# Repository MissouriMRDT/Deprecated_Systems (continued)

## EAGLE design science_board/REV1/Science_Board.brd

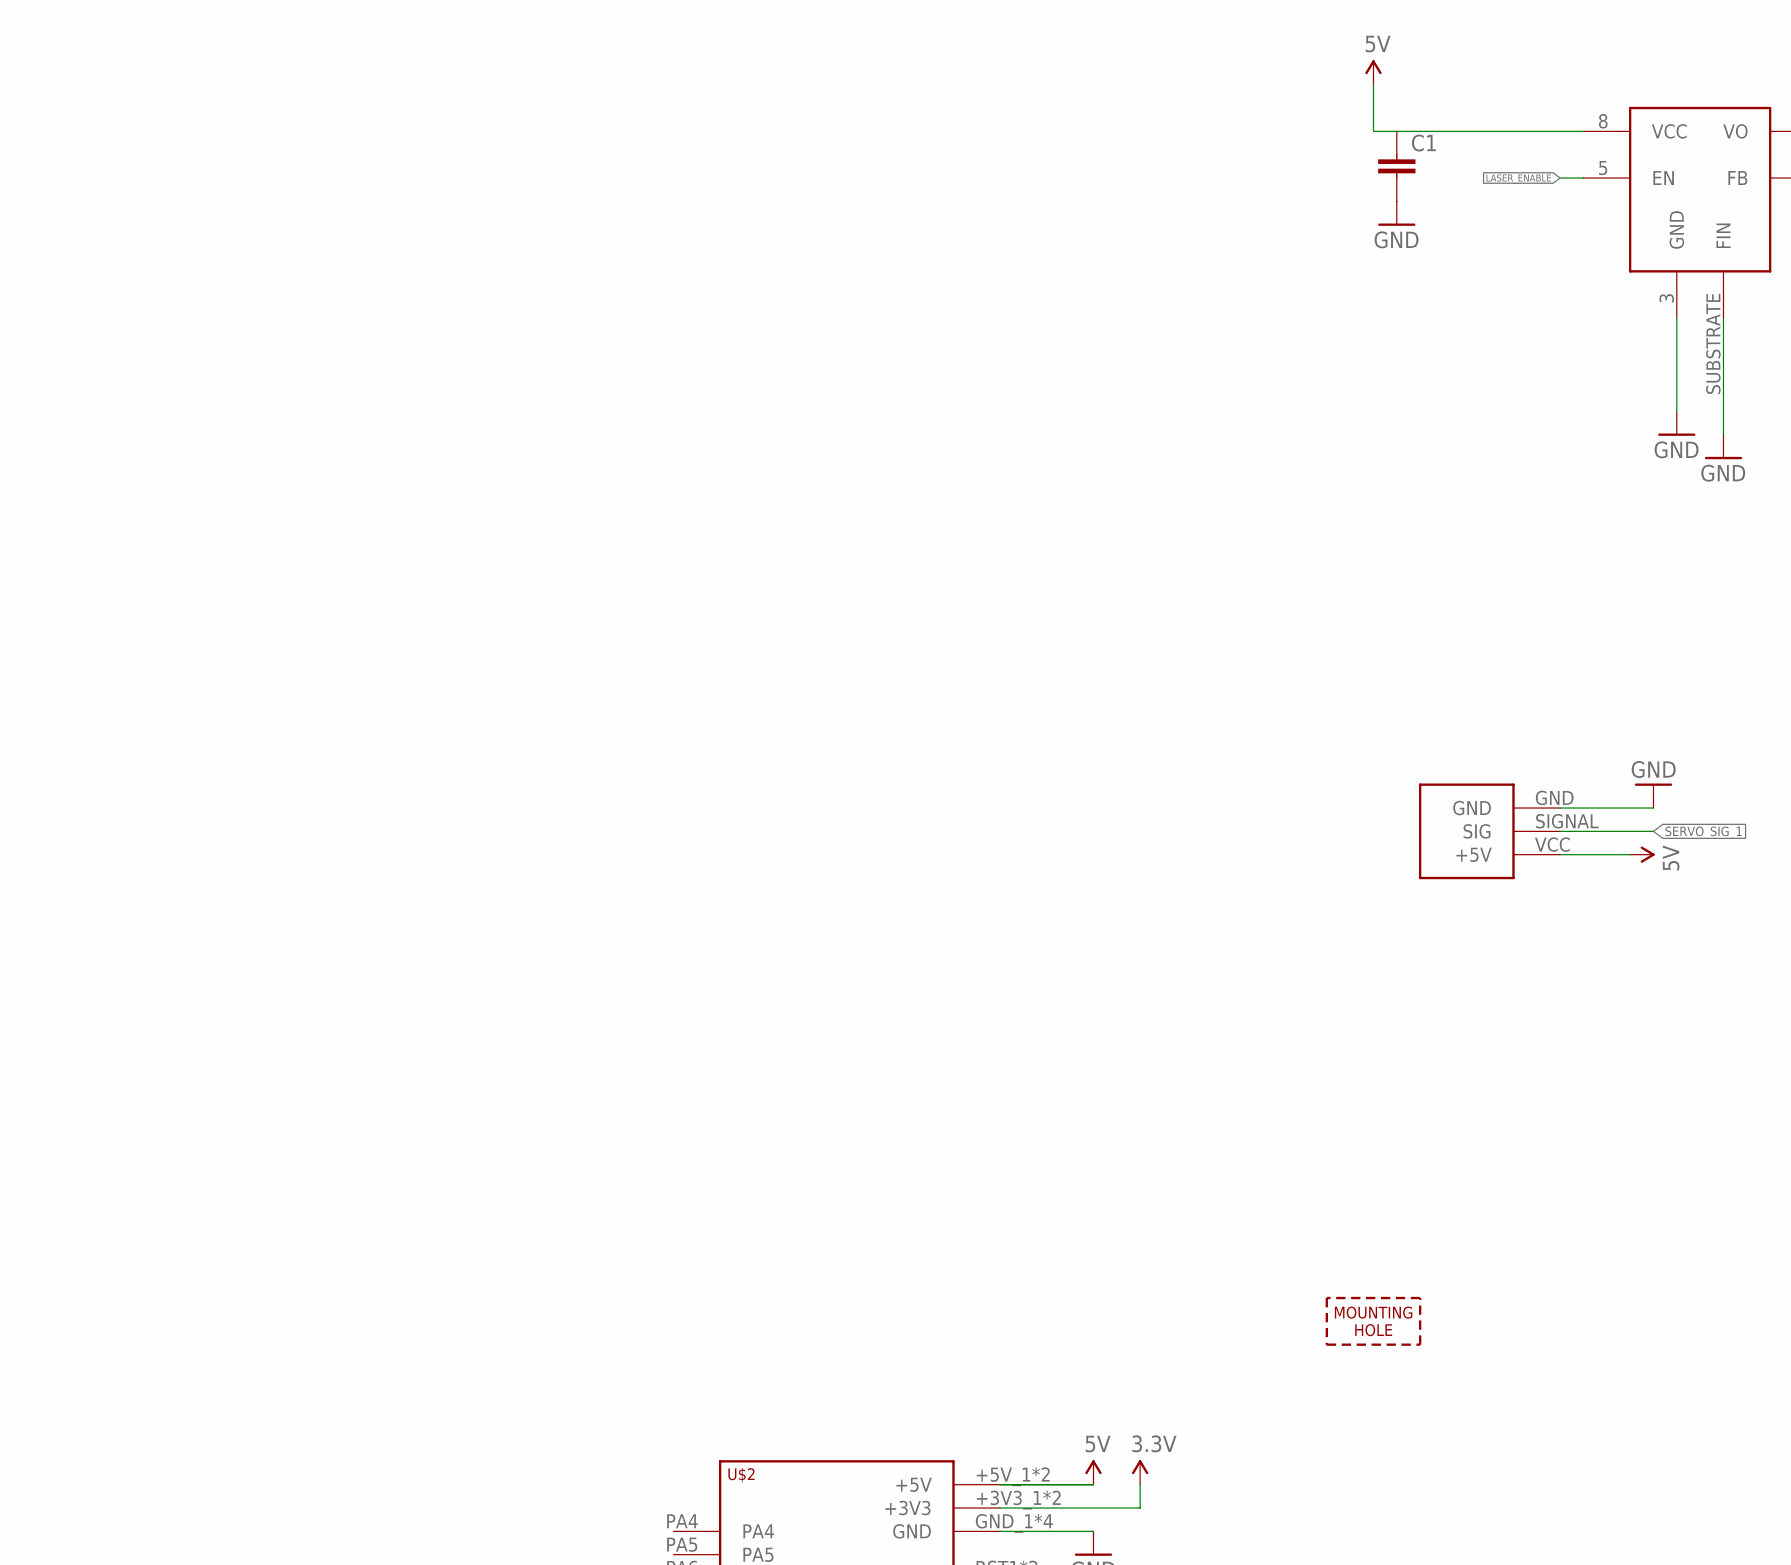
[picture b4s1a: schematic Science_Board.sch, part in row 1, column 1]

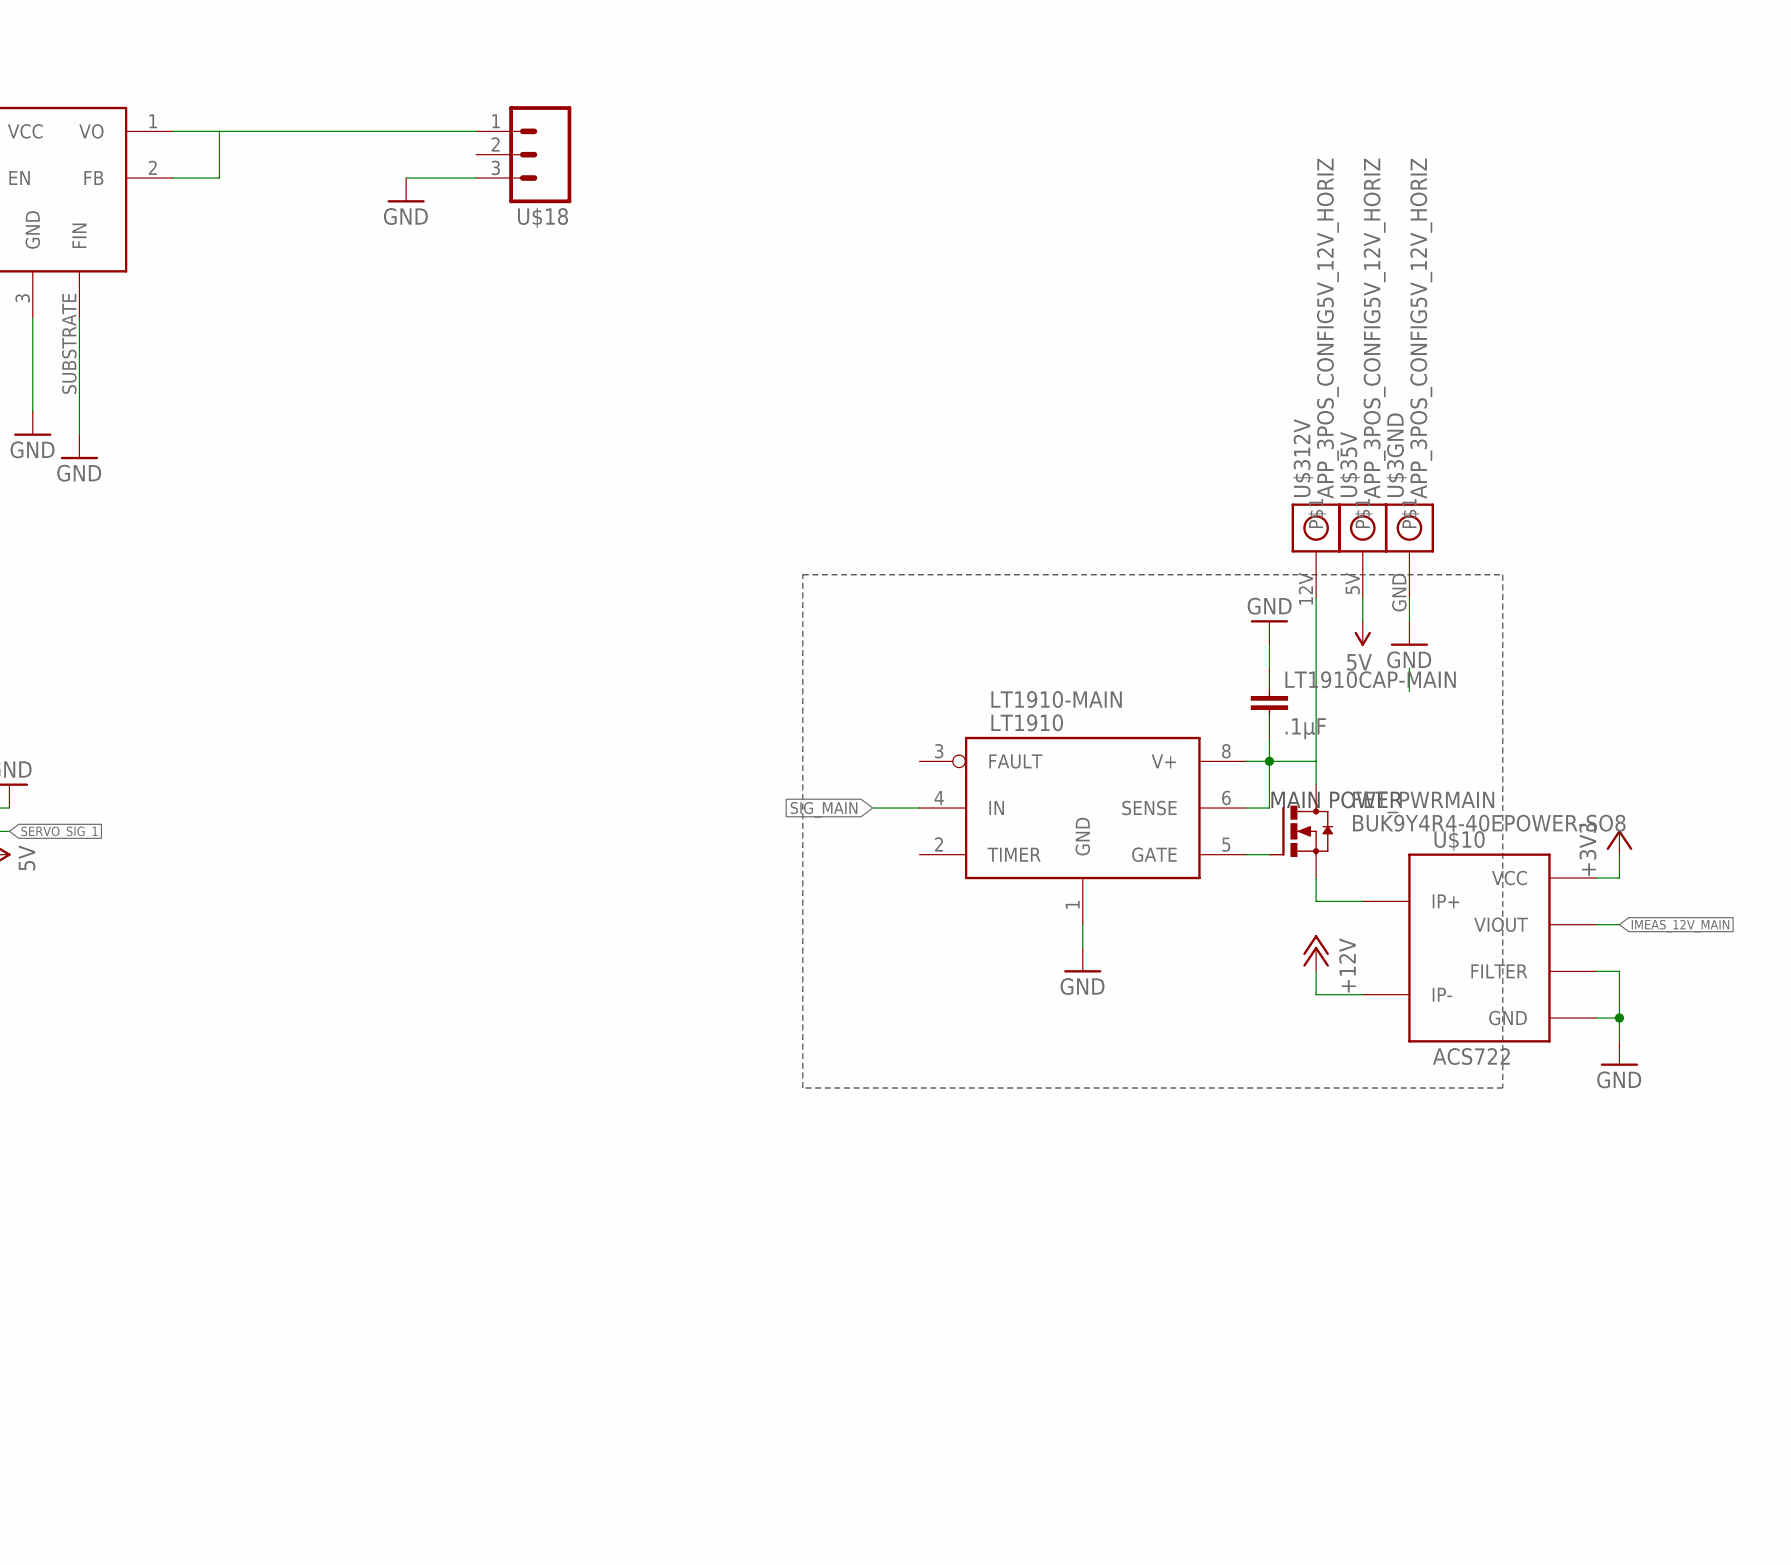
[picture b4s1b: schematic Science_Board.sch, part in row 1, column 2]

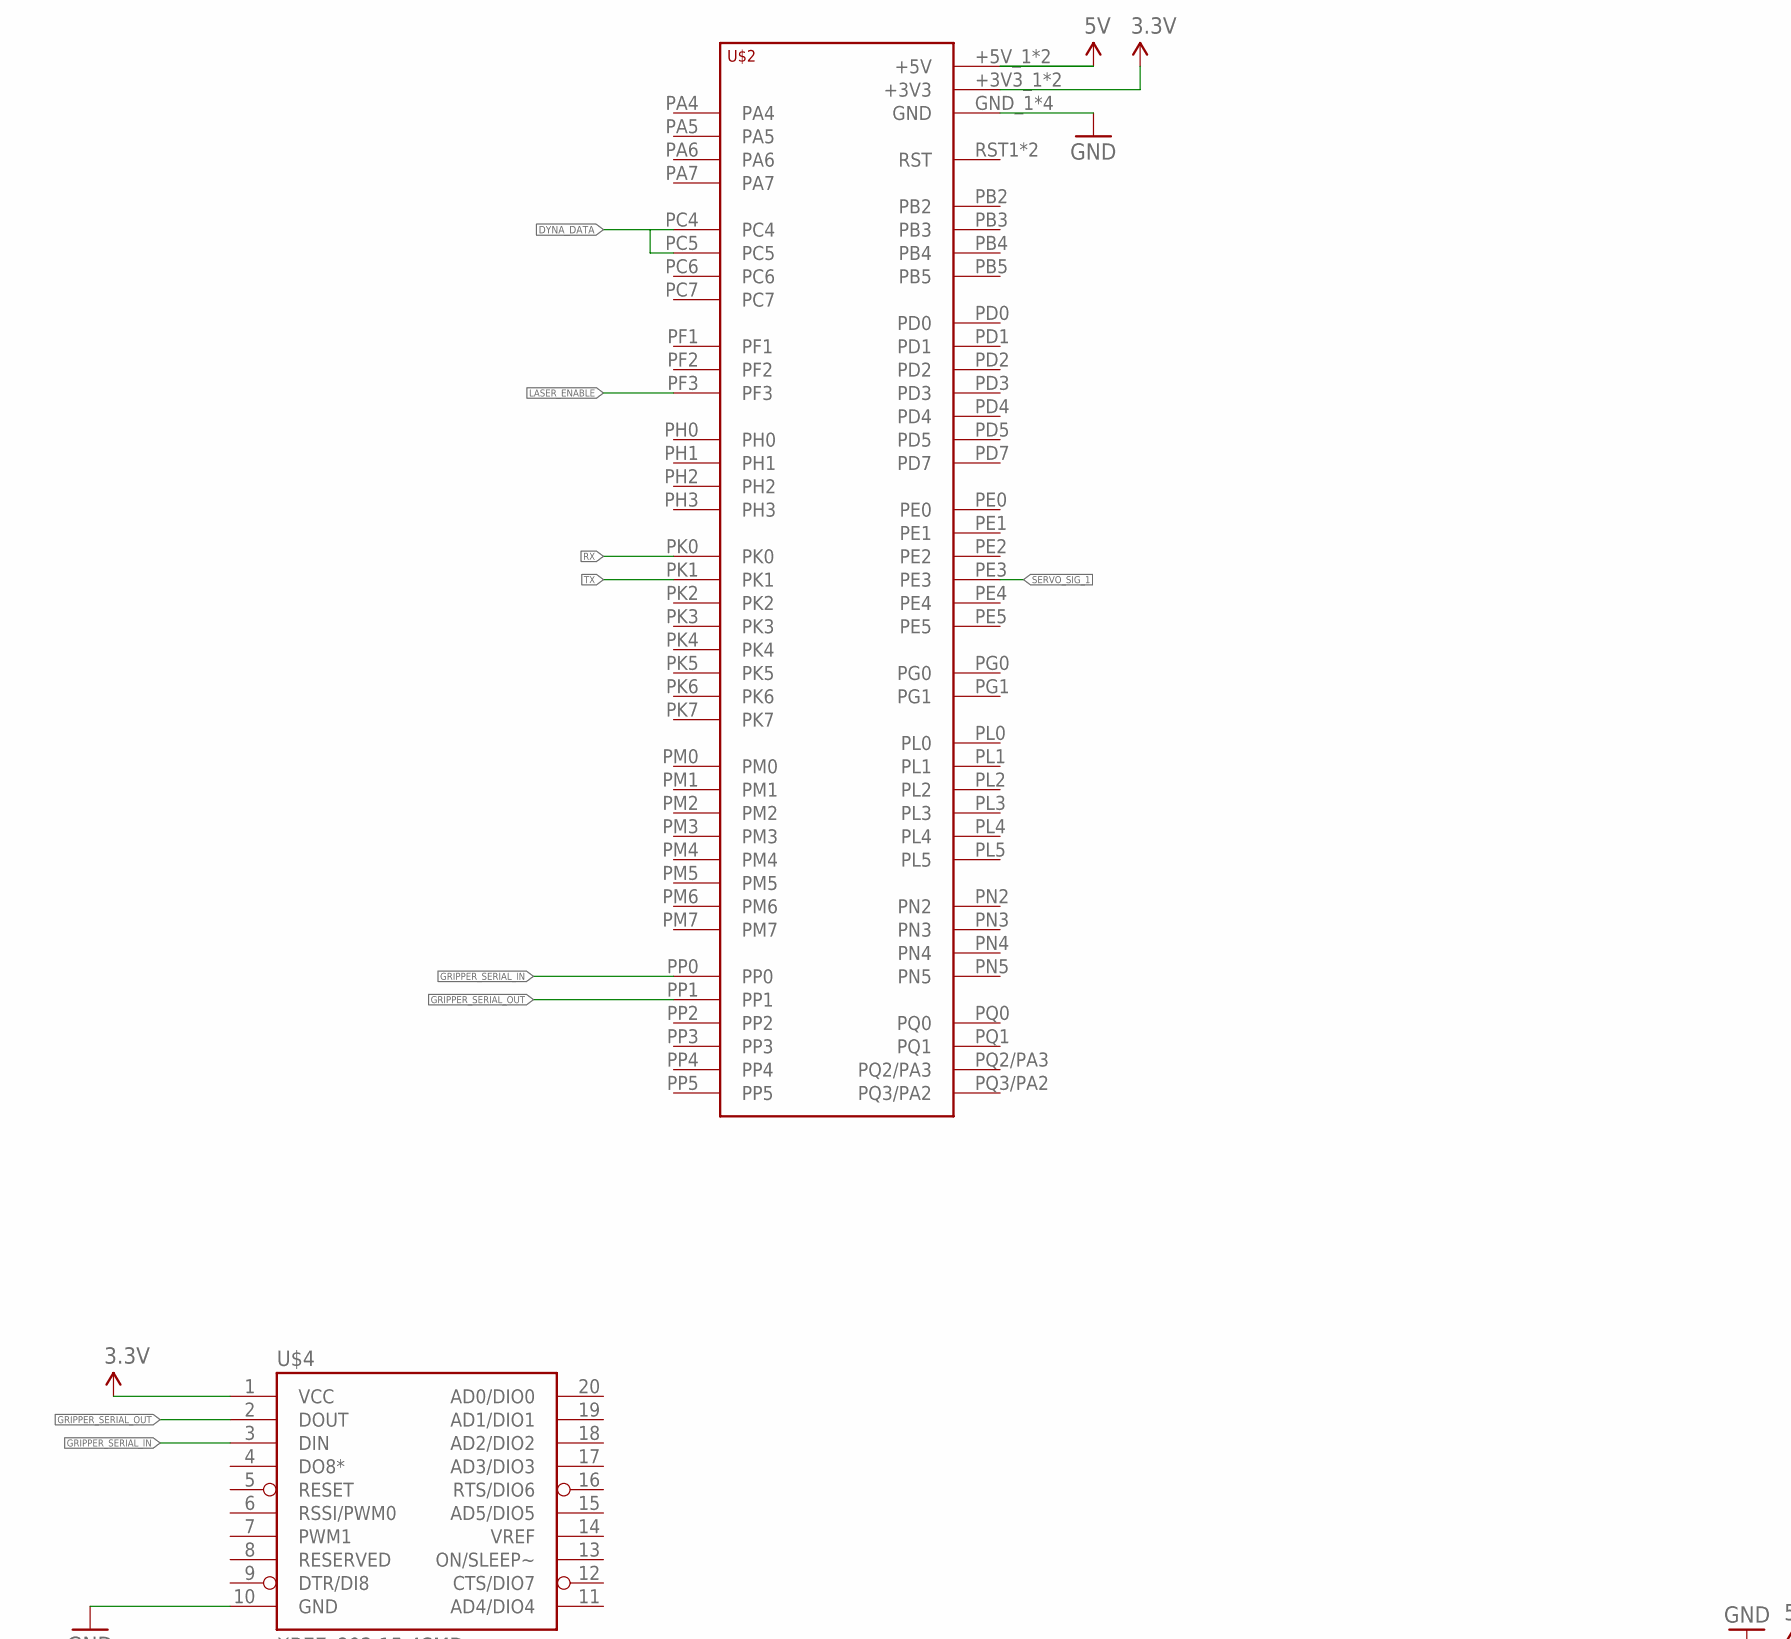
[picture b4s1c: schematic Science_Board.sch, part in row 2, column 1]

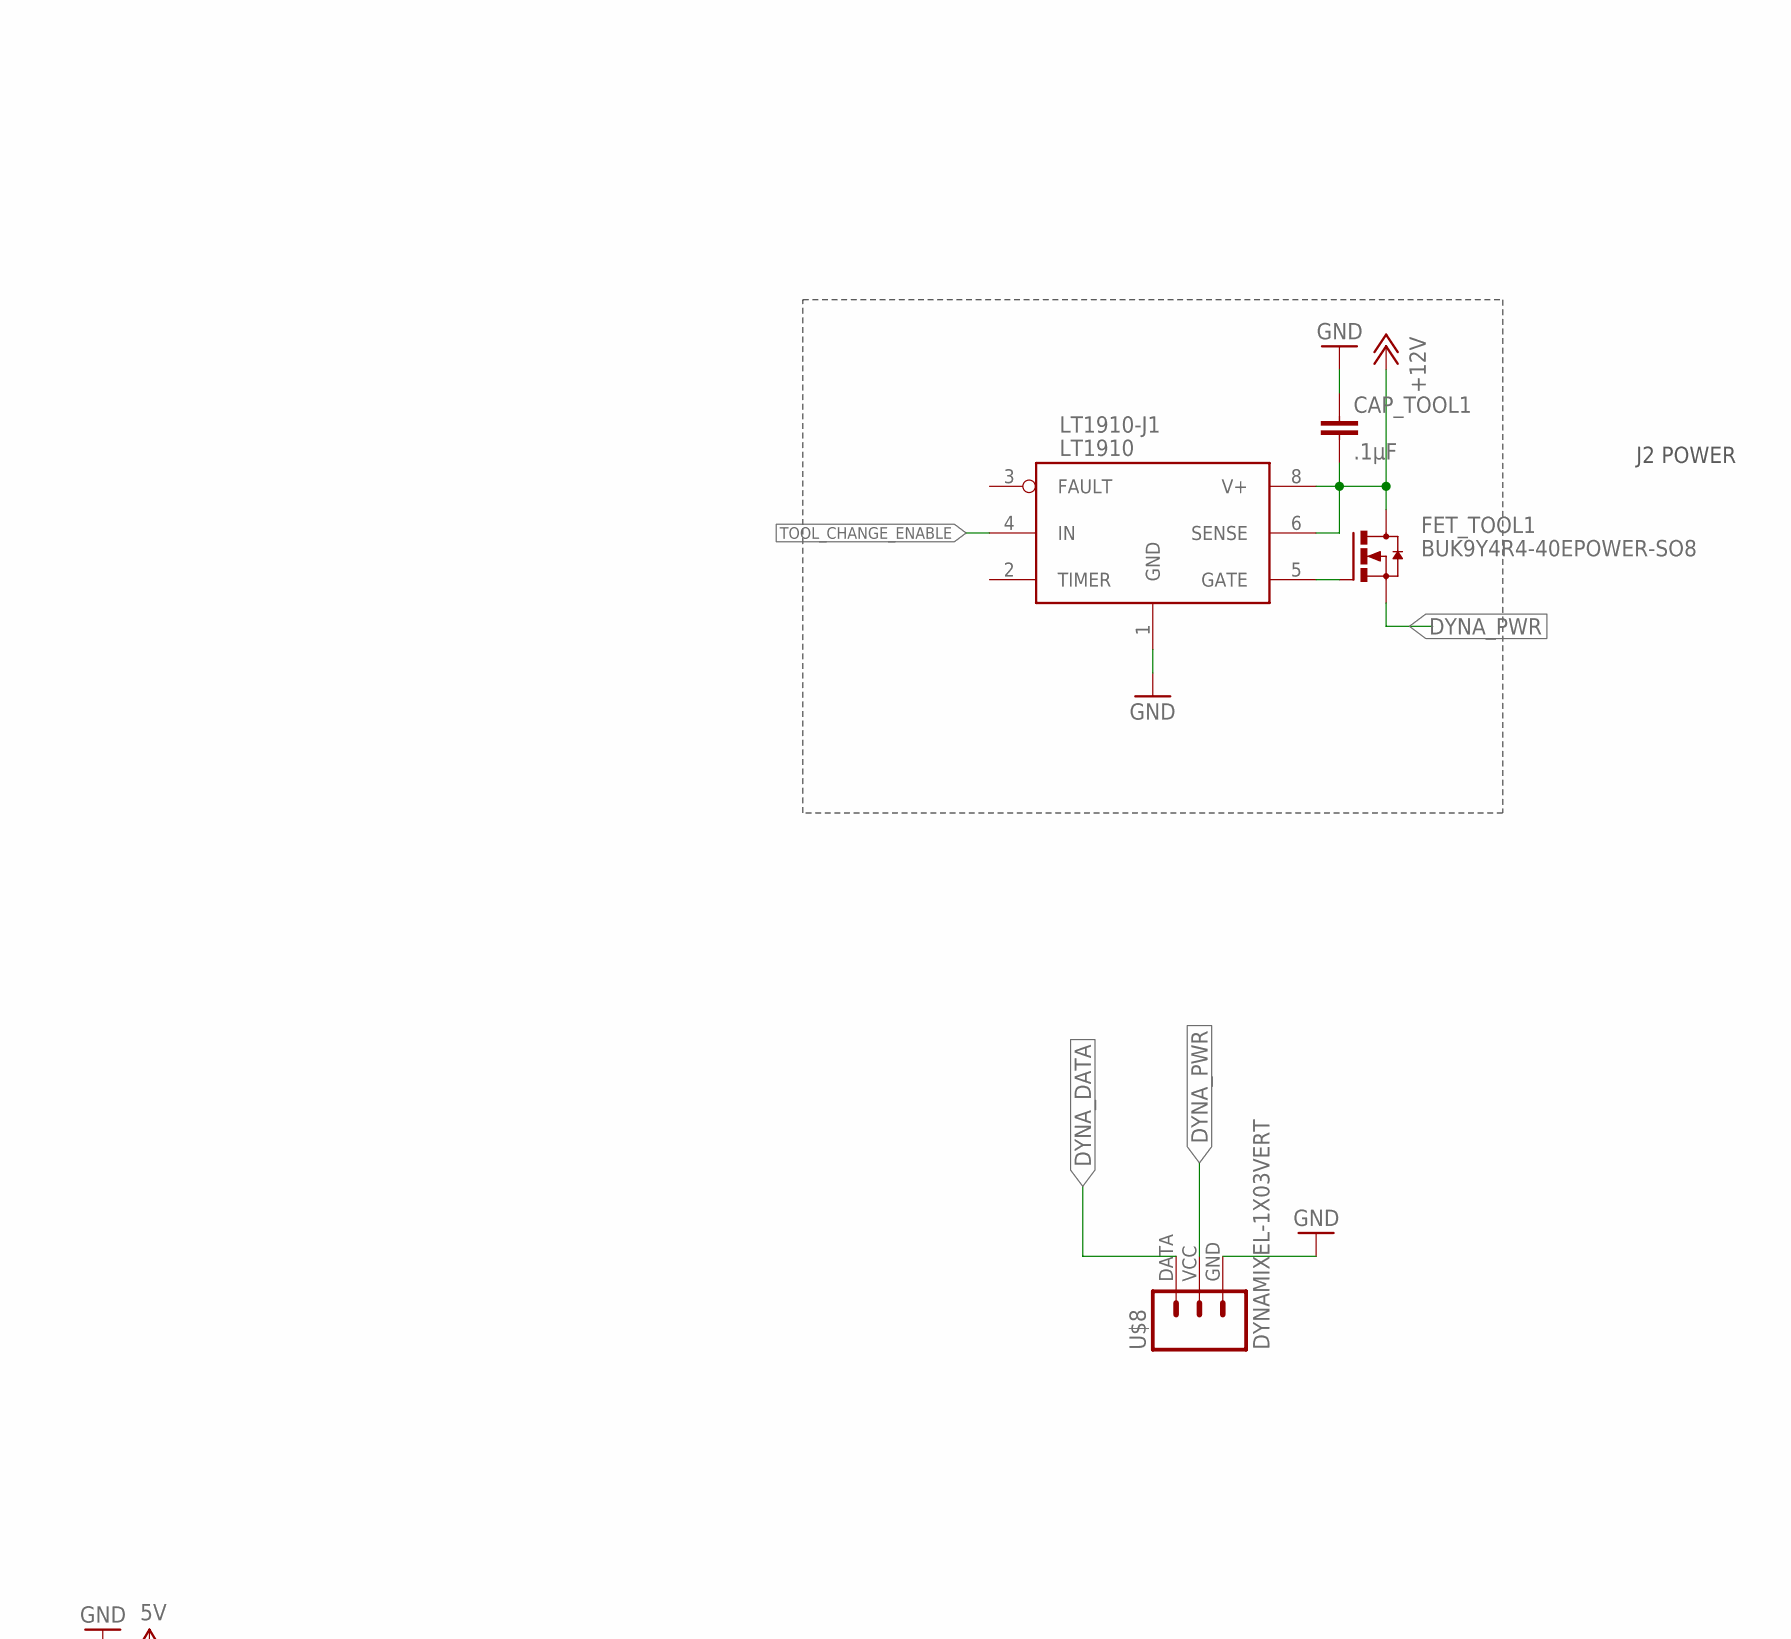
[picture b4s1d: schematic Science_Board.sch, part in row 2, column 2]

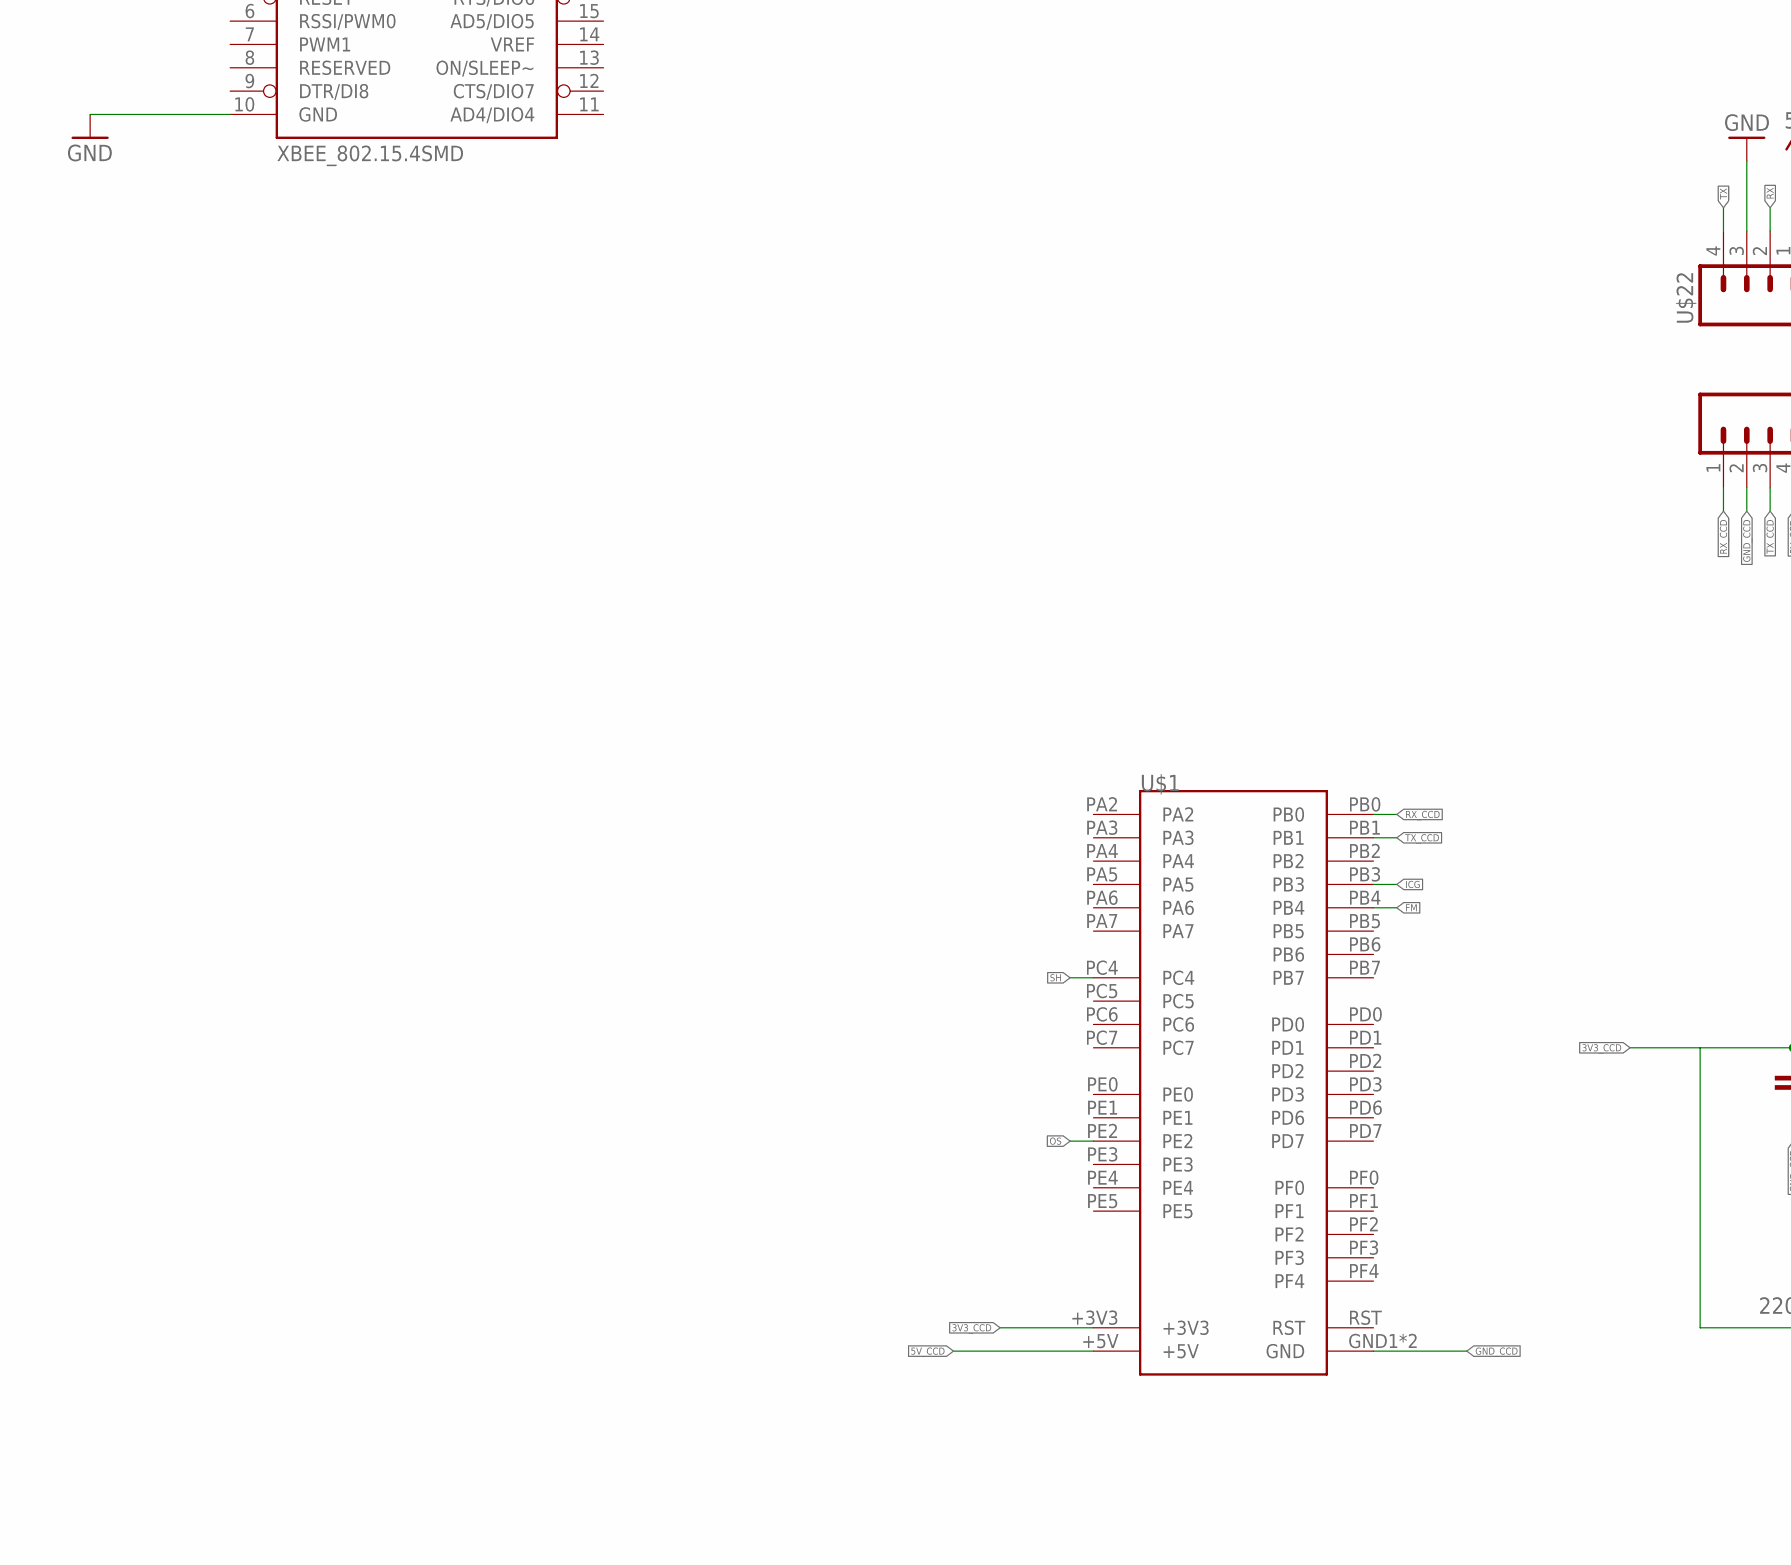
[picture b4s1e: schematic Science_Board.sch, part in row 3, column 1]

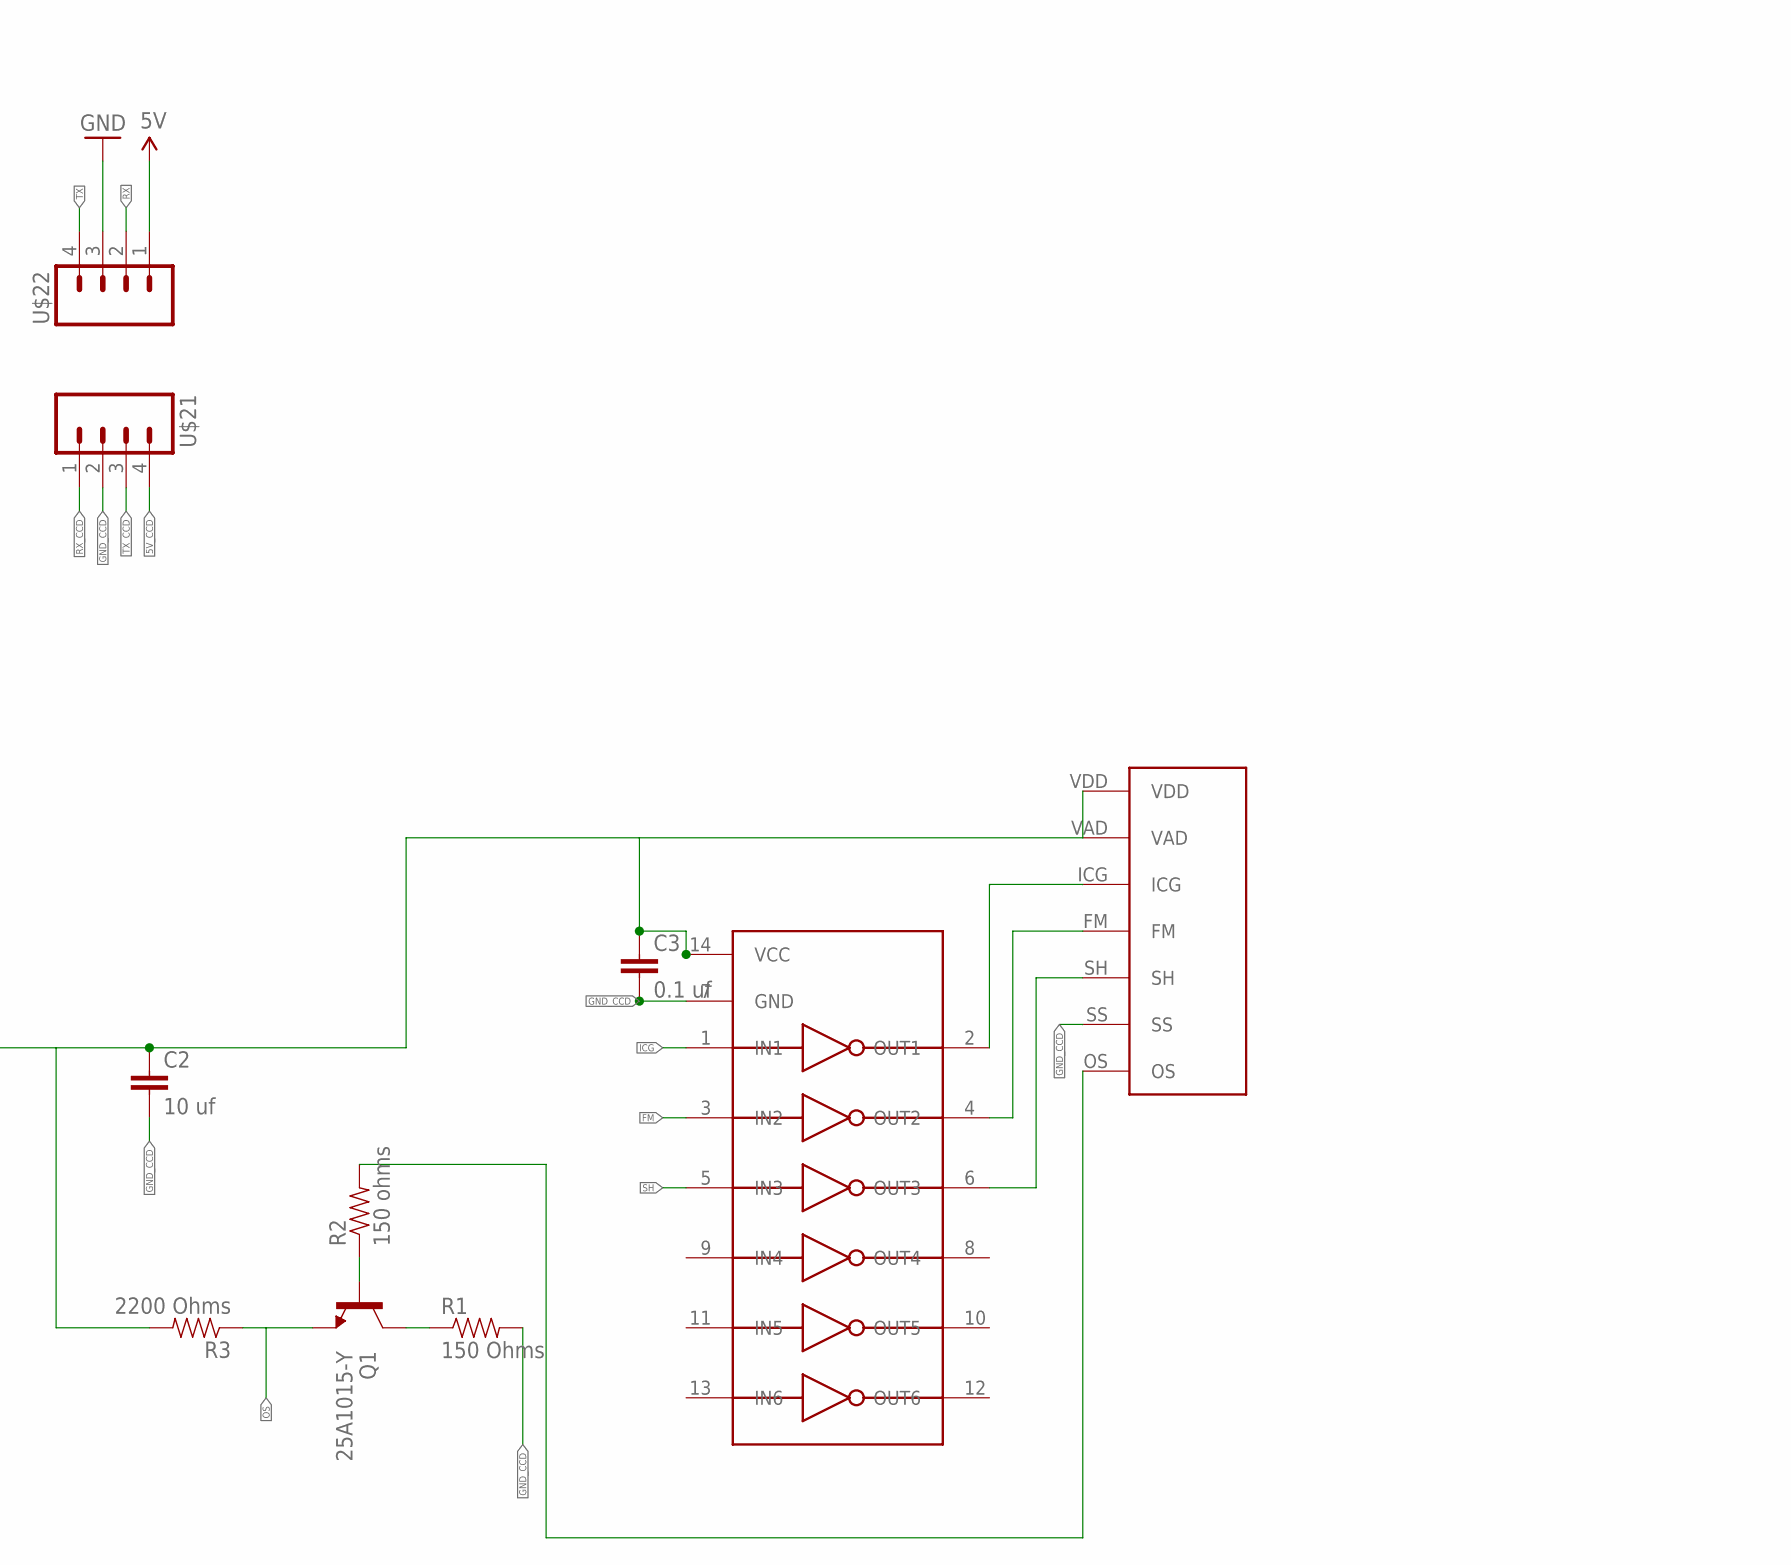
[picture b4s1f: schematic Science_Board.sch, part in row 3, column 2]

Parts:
C1: CAP0603-CAP; 0603-CAP
C2: 10 uf; 0603-CAP
C3: 0.1 uf; 0603-CAP
CAP_TOOL1: .1µF; 0603-CAP
FET_PWRMAIN: BUK9Y4R4-40EPOWER-SO8; POWER-SO8
FET_TOOL1: BUK9Y4R4-40EPOWER-SO8; POWER-SO8
LT1910-J1, LT1910-MAIN: LT1910; SO8
LT1910CAP-MAIN: .1µF; 0603-CAP
Q1: 25A1015-Y; TO-92-AMMO
R1: 150 Ohms; 0603-RES
R2: 150 ohms; 0603-RES
R3: 2200 Ohms; 0603-RES
U$1: TIVA-C
U$2: TIVA-C-CONNECTED
U$3: APP_3POS_CONFIG5V_12V_HORIZ; APP45_5V_12V_HORIZ_CONFIG
U$4: XBEE_802.15.4SMD; XBEE_802.15.4_SMD
U$6: MOUNTING_HOLE#8; #8_SCREW
U$8: DYNAMIXEL-1X03VERT; MLX-SPOX5267-3PIN
U$9: 3V_LDO_REGULATOR; SO8
U$10: ACS722; SO-08
U$11: TC74HC04AP; DIP14
U$12: TCD1304DG; CCD_PACKAGE
U$17: SERVO; SERVO_JACK
U$18: M03; MOLEX_0436500300
U$21, U$22: M04; MOLEX_0436500400

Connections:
3.3V: U$2.+3V3_1 (+3V3), U$2.+3V3_2 (+3V3), U$4.1 (VCC)
3V3_CCD: C2.1, C3.1, R3.2, U$1.+3V3, U$11.14 (VCC), U$12.VAD, U$12.VDD
3V_REGULATED: U$9.1 (VO), U$9.2 (FB), U$18.1
5V: U$22.1
5V_CCD: U$1.+5V, U$21.4
+3V3: U$10.8 (VCC)
+5V: C1.1, U$2.+5V_1 (+5V), U$2.+5V_2 (+5V), U$3.5V, U$9.8 (VCC), U$17.VCC (+5V)
+12V: CAP_TOOL1.2, FET_TOOL1.5 (D), FET_TOOL1.6 (D), FET_TOOL1.7 (D), FET_TOOL1.8 (D), LT1910-J1.6 (SENSE), LT1910-J1.8 (V+), U$10.3 (IP-), U$10.4 (IP-)
DYNA_DATA: U$2.PC4, U$2.PC5, U$8.DATA
DYNA_PWR: FET_TOOL1.1 (S), FET_TOOL1.2 (S), FET_TOOL1.3 (S), U$8.VCC
FM: U$1.PB4, U$11.3 (IN2)
GATE-J1: FET_TOOL1.4 (G), LT1910-J1.5 (GATE)
GATE-MAIN: FET_PWRMAIN.4 (G), LT1910-MAIN.5 (GATE)
GND: C1.2, CAP_TOOL1.1, LT1910-J1.1 (GND), LT1910-MAIN.1 (GND), LT1910CAP-MAIN.1, U$2.GND_1 (GND), U$2.GND_2 (GND), U$2.GND_3 (GND), U$2.GND_4 (GND), U$3.GND, U$4.10 (GND), U$8.GND, U$9.3 (GND), U$9.SUBSTRATE (FIN), U$10.5 (GND), U$10.6 (FILTER), U$17.GND, U$18.3, U$22.3
GND_CCD: C2.2, C3.2, R1.2, U$1.GND1 (GND), U$1.GND2 (GND), U$11.7 (GND), U$12.SS, U$21.2
GRIPPER_SERIAL_IN: U$2.PP0, U$4.3 (DIN)
GRIPPER_SERIAL_OUT: U$2.PP1, U$4.2 (DOUT)
ICG: U$1.PB3, U$11.1 (IN1)
IMEAS_12V_MAIN: U$10.7 (VIOUT)
LASER_ENABLE: U$2.PF3, U$9.5 (EN)
unnamed: FET_PWRMAIN.5 (D), FET_PWRMAIN.6 (D), FET_PWRMAIN.7 (D), FET_PWRMAIN.8 (D), LT1910-MAIN.6 (SENSE), LT1910-MAIN.8 (V+), LT1910CAP-MAIN.2, U$3.12V
unnamed: Q1.1 (C), R1.1
unnamed: Q1.2 (B), R2.1
unnamed: U$11.2 (OUT1), U$12.ICG
unnamed: U$11.4 (OUT2), U$12.FM
unnamed: U$11.6 (OUT3), U$12.SH
unnamed: R2.2, U$12.OS
OS: Q1.3 (E), R3.1, U$1.PE2
RST: U$1.RST
RX: U$2.PK0, U$22.2
RX_CCD: U$1.PB0, U$21.1
SERVO_SIG_1: U$2.PE3, U$17.SIGNAL (SIG)
SH: U$1.PC4, U$11.5 (IN3)
SIG_MAIN: LT1910-MAIN.4 (IN)
SOURCE-MAIN: FET_PWRMAIN.1 (S), FET_PWRMAIN.2 (S), FET_PWRMAIN.3 (S), U$10.1 (IP+), U$10.2 (IP+)
TOOL_CHANGE_ENABLE: LT1910-J1.4 (IN)
TX: U$2.PK1, U$22.4
TX_CCD: U$1.PB1, U$21.3

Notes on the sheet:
MAIN POWER
J2 POWER

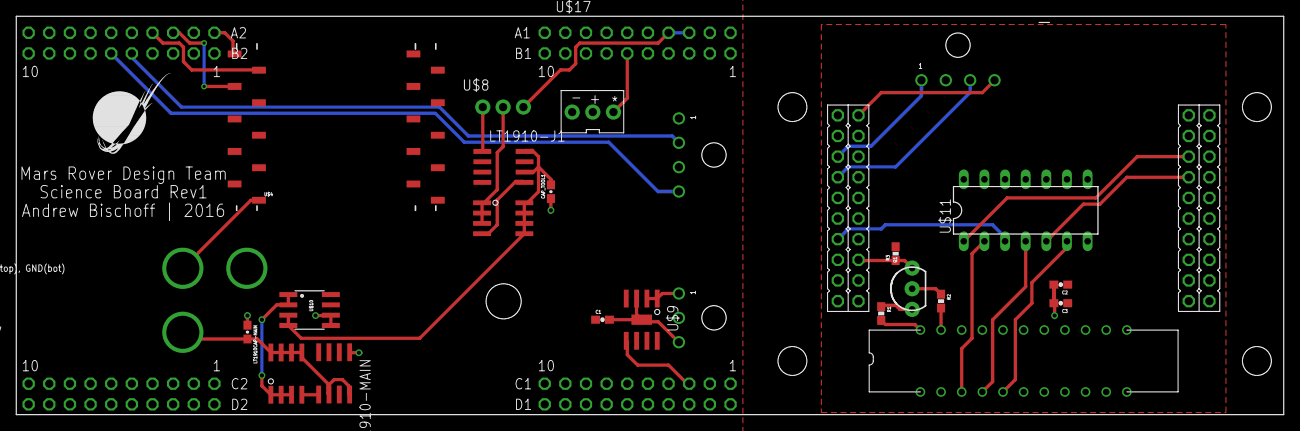
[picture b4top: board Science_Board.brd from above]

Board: 2 copper layers, 156.0 x 49.0 mm, 33 parts (0 on the bottom side), 32 nets.

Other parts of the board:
U$5: MOUNTING_HOLE#8; #8_SCREW
U$7: MRDT_LOGO
U$13, U$14, U$15, U$16: #6_SCREW

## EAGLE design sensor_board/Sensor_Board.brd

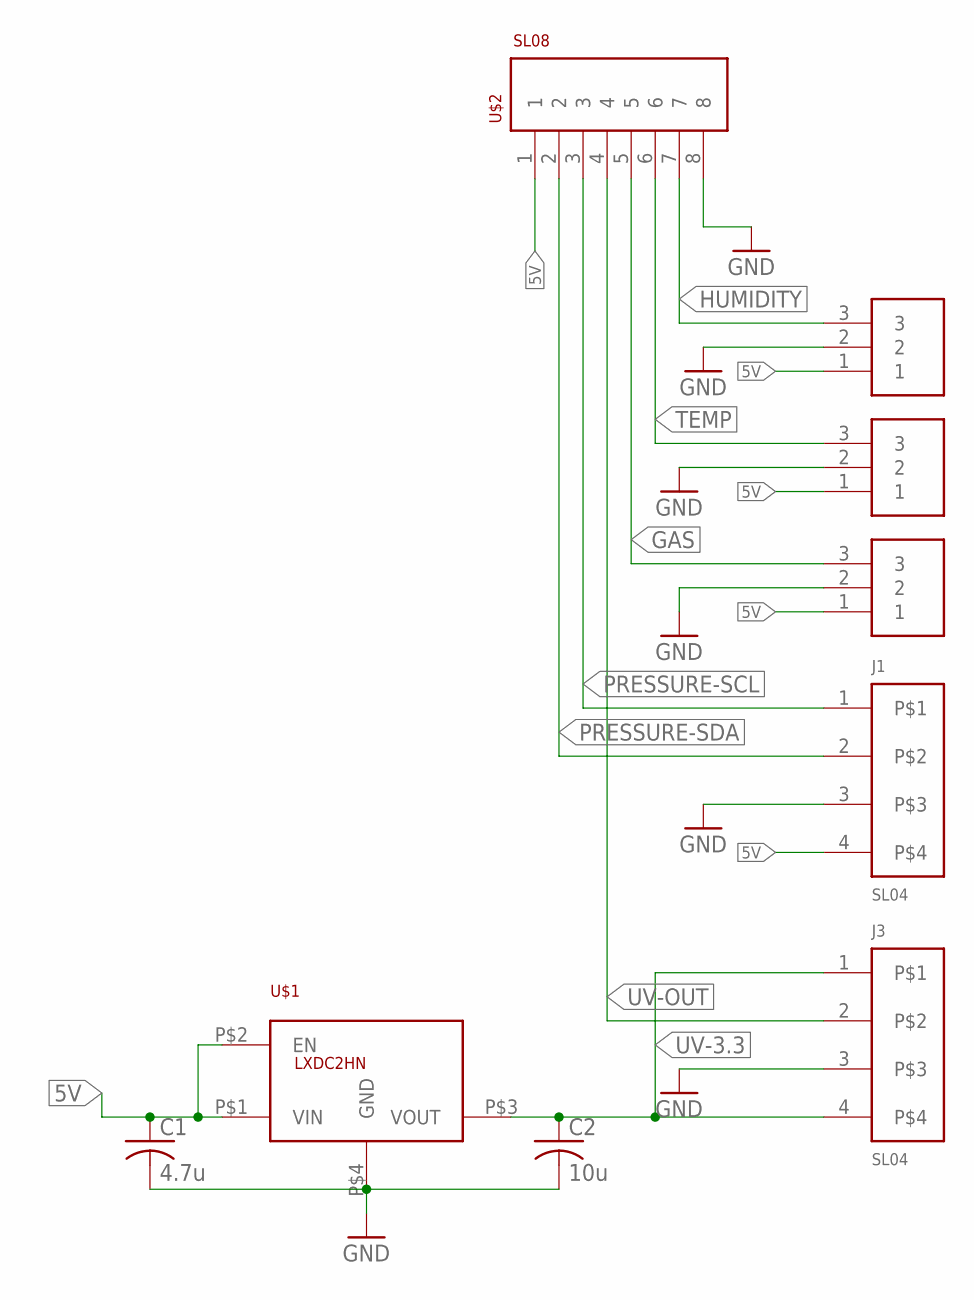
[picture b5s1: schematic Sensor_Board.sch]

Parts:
C1: 4.7u; C0805
C2: 10u; C0805
J1, J3: SL04; MOLEX_SL_04_TH
J2, J4, J5: SL03THROUGH_HOLE; MOLEX_SL_03_TH
U$1: LXDC2HN; 4-SMD
U$2: SL08; MOLEX-70543-0007

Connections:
5V: C1.1, J1.4, J2.1, J4.1, J5.1, U$1.P$1 (VIN), U$1.P$2 (EN)
GAS: J5.3, U$2.5
GND: C1.2, C2.2, J1.3, J2.2, J3.3, J4.2, J5.2, U$1.P$4 (GND), U$2.8
HUMIDITY: J2.3, U$2.7
PRESSURE-SCL: J1.1, U$2.3
PRESSURE-SDA: J1.2, U$2.2
TEMP: J4.3, U$2.6
UV-3.3: C2.1, J3.1, J3.4, U$1.P$3 (VOUT)
UV-OUT: J3.2, U$2.4

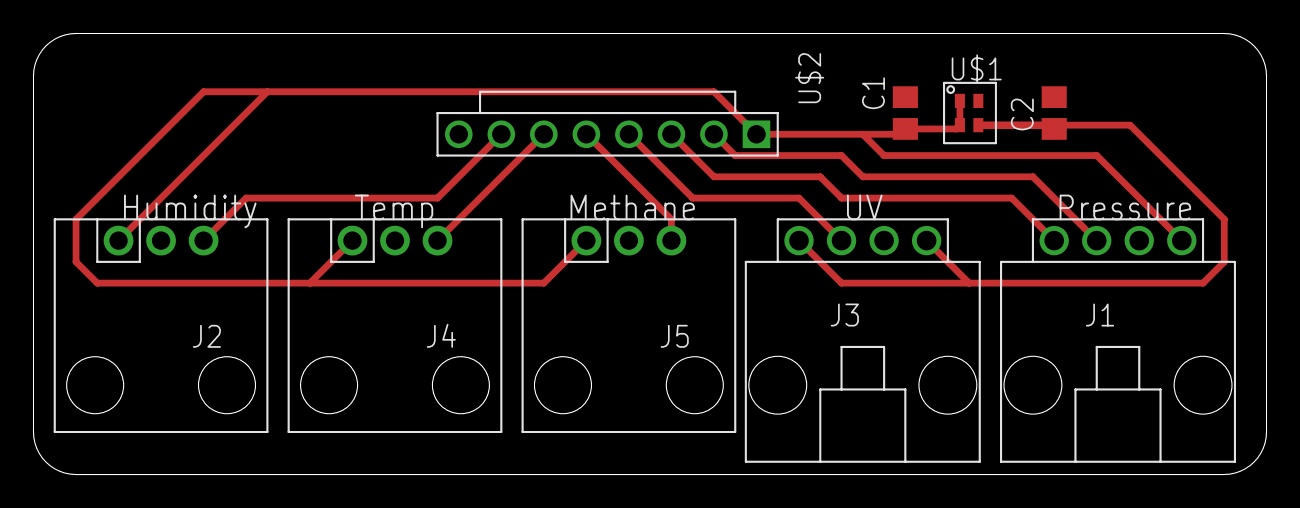
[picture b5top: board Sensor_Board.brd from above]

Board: 2 copper layers, 73.6 x 26.3 mm, 9 parts (0 on the bottom side), 9 nets.
